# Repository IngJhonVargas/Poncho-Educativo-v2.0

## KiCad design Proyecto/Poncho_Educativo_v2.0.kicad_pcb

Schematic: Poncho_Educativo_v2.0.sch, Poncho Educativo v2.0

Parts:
F1, F2, F3: FIDUCIAL; Fiducial_1mm

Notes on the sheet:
Fiduciales

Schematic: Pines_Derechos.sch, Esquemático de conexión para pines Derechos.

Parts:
AFF1: CA56-12; Cx56-12; Digikey# 67-1442-ND
M1: Matrix_8x8_LED; Matrix_8x8_LEDs; Digikey# TA15-11EWA-ND
R1, R2: 9.53k; R_0805_HandSoldering; Digikey# P21131TR-ND
U1, U2: MAX7219; Digikey# MAX7219CWG+-ND
XA2: Conn_Poncho2P_2x_20x2; Conn_Poncho_Derecha

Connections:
+5V: R1.1, R2.2, U1.19 (Vcc), U2.19 (Vcc), XA2.2 (+5V); also elsewhere on the board
/Pines Derechos/C0: M1.9, U2.2 (DIG0)
/Pines Derechos/C1: M1.10, U2.11 (DIG1)
/Pines Derechos/C2: M1.14, U2.6 (DIG2)
/Pines Derechos/C3: M1.3, U2.7 (DIG3)
/Pines Derechos/C4: M1.15, U2.3 (DIG4)
/Pines Derechos/C5: M1.5, U2.10 (DIG5)
/Pines Derechos/C6: M1.6, U2.5 (DIG6)
/Pines Derechos/C7: M1.12, U2.8 (DIG7)
/Pines Derechos/CLK: U1.13 (CLK), U2.13 (CLK), XA2.33 (tecF0)
/Pines Derechos/D0: AFF1.12 (CA1), U1.2 (DIG0)
/Pines Derechos/D1: AFF1.9 (CA2), U1.11 (DIG1)
/Pines Derechos/D2: AFF1.8 (CA3), U1.6 (DIG2)
/Pines Derechos/D3: AFF1.6 (CA4), U1.7 (DIG3)
/Pines Derechos/Din: U1.1 (DIN), U2.1 (DIN), XA2.39 (tecCOL0)
/Pines Derechos/F0: M1.7, U2.14 (SEGa)
/Pines Derechos/F1: M1.2, U2.16 (SEGb)
/Pines Derechos/F2: M1.8, U2.20 (SEGc)
/Pines Derechos/F3: M1.13, U2.23 (SEGd)
/Pines Derechos/F4: M1.1, U2.21 (SEGe)
/Pines Derechos/F5: M1.11, U2.15 (SEGf)
/Pines Derechos/F6: M1.16, U2.17 (SEGg)
/Pines Derechos/F7: M1.4, U2.22 (SEGdp)
/Pines Derechos/LOAD1: U1.12 (LOAD(cs)), XA2.37 (tecF2)
/Pines Derechos/LOAD2: U2.12 (LOAD(cs)), XA2.35 (tecF3)
/Pines Derechos/S0: AFF1.11 (a), U1.14 (SEGa)
/Pines Derechos/S1: AFF1.7 (b), U1.16 (SEGb)
/Pines Derechos/S2: AFF1.4 (c), U1.20 (SEGc)
/Pines Derechos/S3: AFF1.2 (d), U1.23 (SEGd)
/Pines Derechos/S4: AFF1.1 (e), U1.21 (SEGe)
/Pines Derechos/S5: AFF1.10 (f), U1.15 (SEGf)
/Pines Derechos/S6: AFF1.5 (g), U1.17 (SEGg)
/Pines Derechos/S7: AFF1.3 (DP), U1.22 (SEGdp)
unnamed 45: R1.2; also elsewhere on the board
unnamed 47: R2.1; also elsewhere on the board
unnamed 52: U1.18 (ISET); also elsewhere on the board
unnamed 53: U2.18 (ISET); also elsewhere on the board

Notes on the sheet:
GND con etiqueta global para el MAX7219 de la matriz de LEDs
En los Integrados MAX7219: Los cátodos son - DIG0 al DIG 7. Los ánodos son SEGa al SEGg y SEGdp

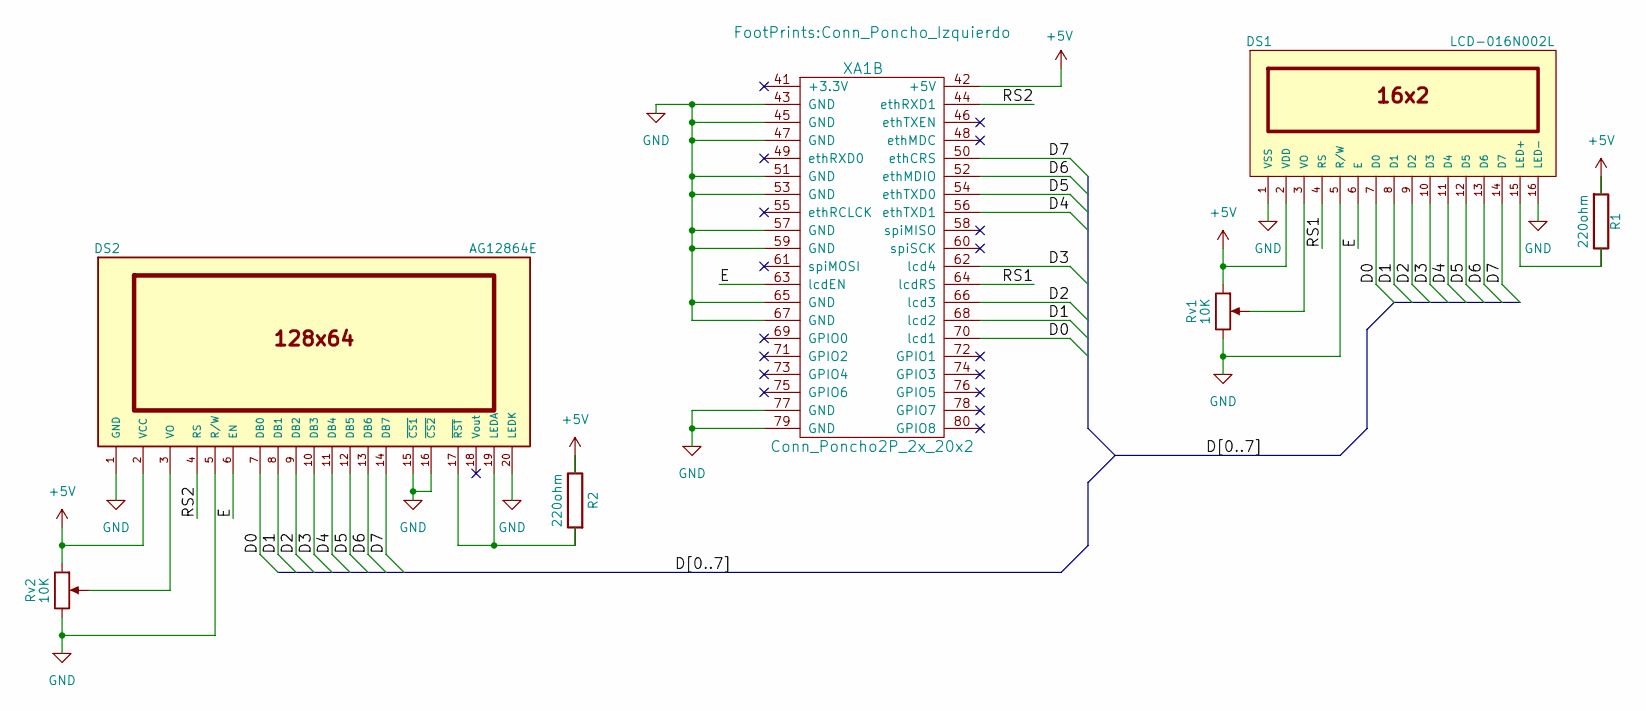
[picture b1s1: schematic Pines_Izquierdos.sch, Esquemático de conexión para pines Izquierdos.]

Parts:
DS1: LCD-016N002L; Digikey# NHD-0216K1Z-NS(RGB)-FBW-REV1-ND
DS2: AG12864E; Digikey# NHD-12864WG-BTMI-V#N-ND
R1, R2: 220ohm; R_0805_HandSoldering; Digikey# P20941TR-ND
Rv1, Rv2: 10K; POT_SMD; Digikey# 3310P-025-103L-ND
XA1: Conn_Poncho2P_2x_20x2; Conn_Poncho_Izquierdo

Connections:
+5V: DS1.2 (VDD), DS2.2 (VCC), R1.1, R2.2, Rv1.1, Rv2.1, XA1.42 (+5V); also elsewhere on the board
/Pines Izquierdos/D0: DS1.7 (D0), DS2.7 (DB0), XA1.70 (lcd1)
/Pines Izquierdos/D1: DS1.8 (D1), DS2.8 (DB1), XA1.68 (lcd2)
/Pines Izquierdos/D2: DS1.9 (D2), DS2.9 (DB2), XA1.66 (lcd3)
/Pines Izquierdos/D3: DS1.10 (D3), DS2.10 (DB3), XA1.62 (lcd4)
/Pines Izquierdos/D4: DS1.11 (D4), DS2.11 (DB4), XA1.56 (ethTXD1)
/Pines Izquierdos/D5: DS1.12 (D5), DS2.12 (DB5), XA1.54 (ethTXD0)
/Pines Izquierdos/D6: DS1.13 (D6), DS2.13 (DB6), XA1.52 (ethMDIO)
/Pines Izquierdos/D7: DS1.14 (D7), DS2.14 (DB7), XA1.50 (ethCRS)
/Pines Izquierdos/E: DS1.6 (E), DS2.6 (EN), XA1.63 (lcdEN)
/Pines Izquierdos/RS1: DS1.4 (RS), XA1.64 (lcdRS)
/Pines Izquierdos/RS2: DS2.4 (RS), XA1.44 (ethRXD1)
unnamed: DS1.3 (VO), Rv1.2
unnamed: DS1.15 (LED+), R1.2
unnamed: DS2.3 (VO), Rv2.2
unnamed: DS2.17 (~RST~), DS2.19 (LEDA), R2.1

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
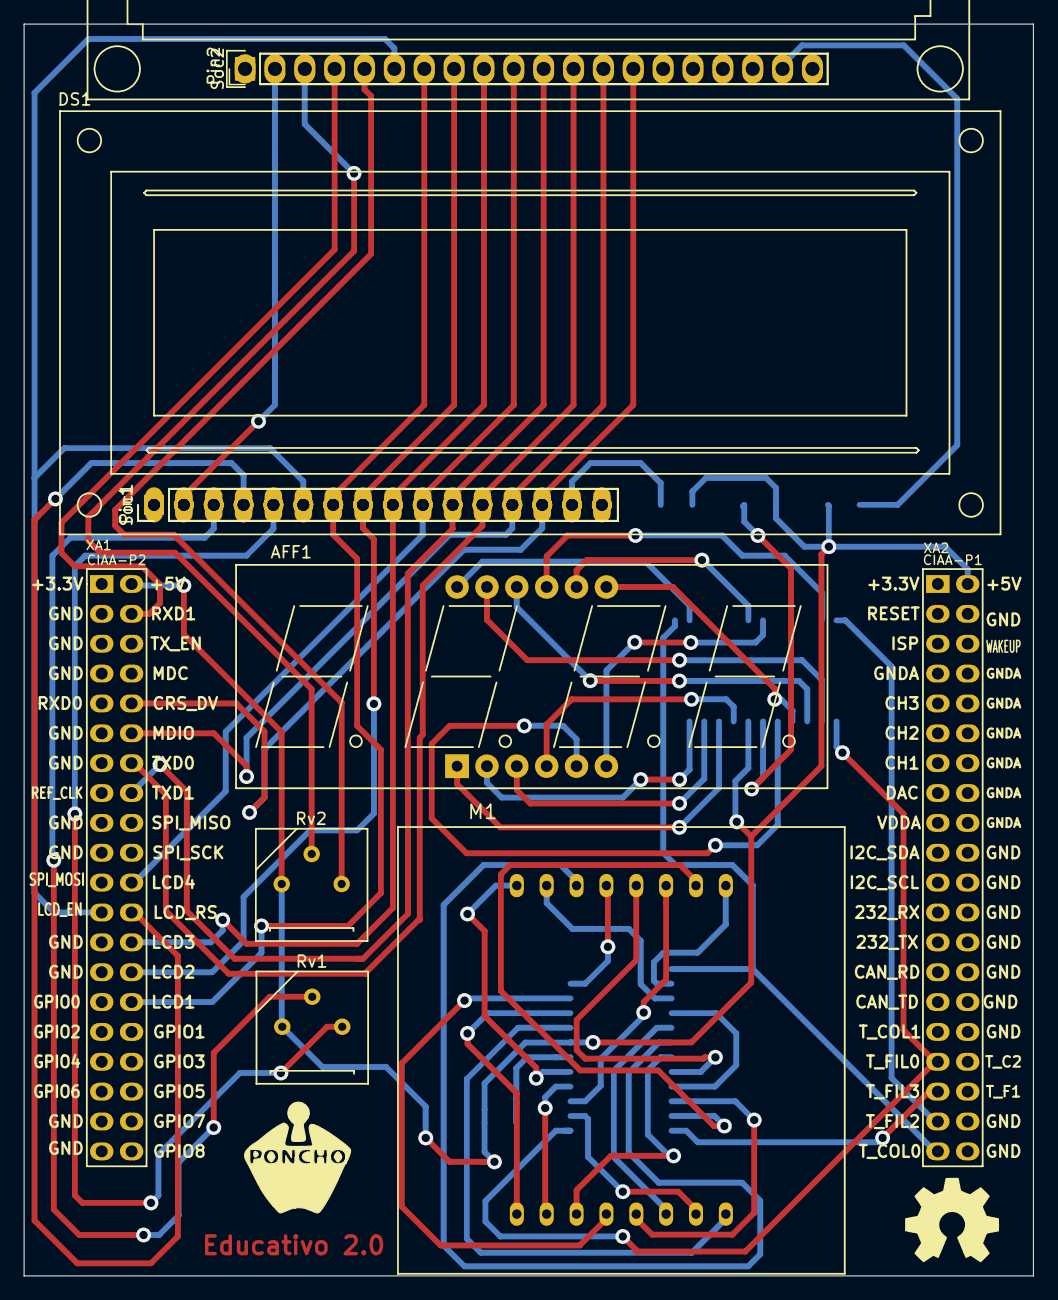
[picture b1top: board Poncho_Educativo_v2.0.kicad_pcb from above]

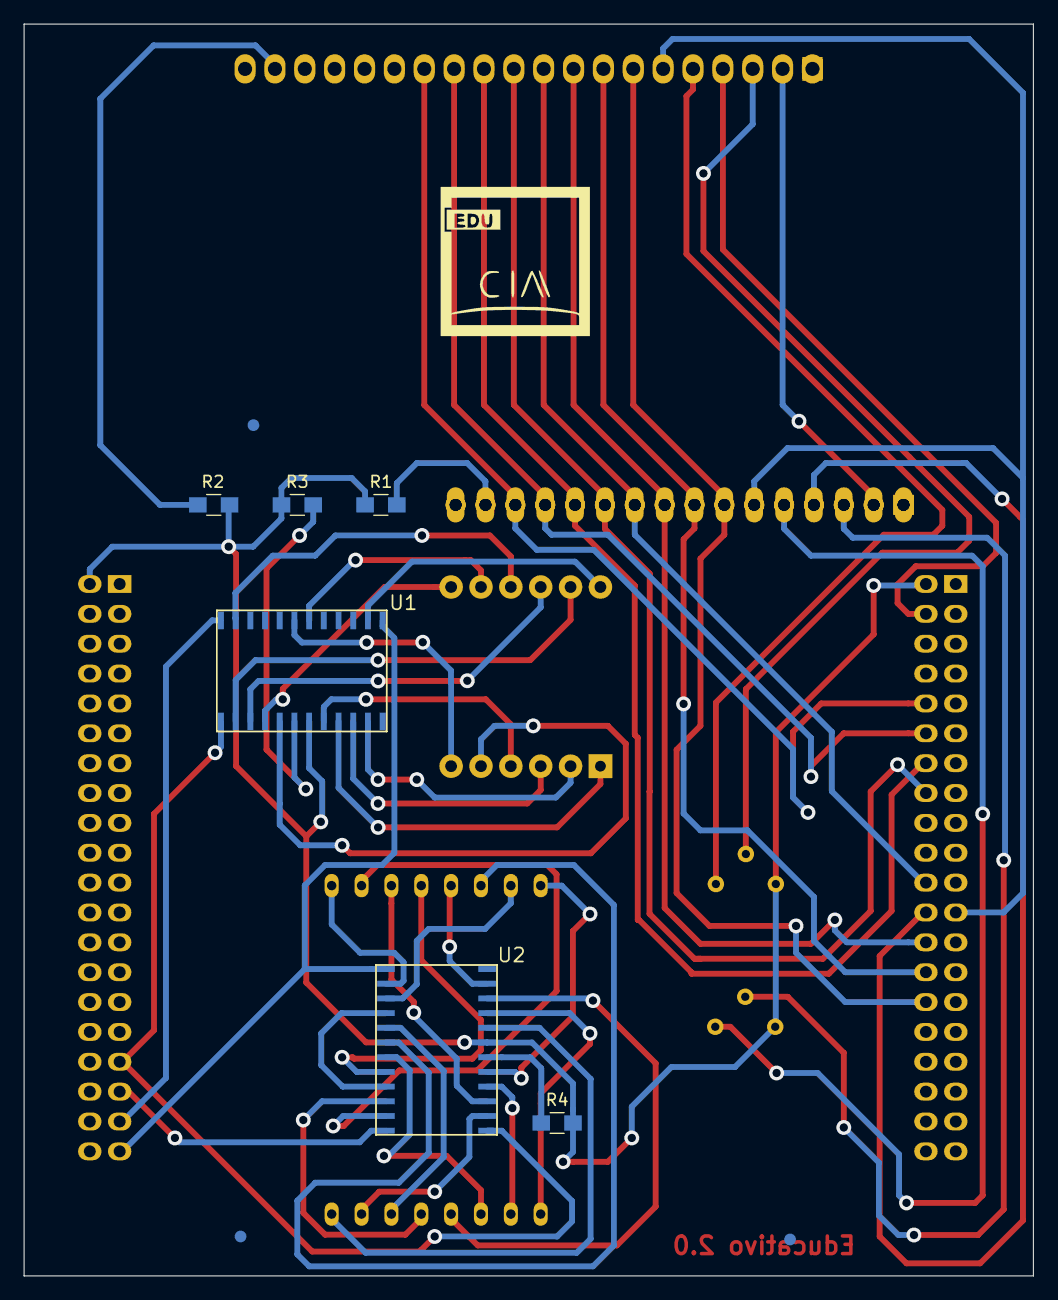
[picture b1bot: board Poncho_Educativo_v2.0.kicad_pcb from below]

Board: 2 copper layers, 85.9 x 106.5 mm, 22 parts (9 on the bottom side), 57 nets.

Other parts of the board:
G101: Logo_OSHWA
Pin1: Pin_Header_Straight_1x16_Pitch2.54mm
Pin2: CONN_01X20; Pin_Header_Straight_1x20
R3, R4: 9.53k; R_0805_HandSoldering
Soc1: Socket_Strip_Straight_1x16_Pitch2.54mm
Soc2: Socket_Strip_Straight_1x20_Pitch2.54mm

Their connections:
+5V: R3.1, R4.1; also elsewhere on the board
unnamed 52: R3.2; also elsewhere on the board
unnamed 53: R4.2; also elsewhere on the board

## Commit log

2017-05-09 Componentes principales.
    Se especificaron los principales componentes que llevará el Poncho
    Educativo v2.0.
2017-05-09 Displays LCD
    Se adjuntó documentación acerca de los 2 Displays LCD.
2017-05-16 Carpetas de displays.
    Se añadieron 2 carpetas para guardar la documentación referente al
    diaplay BCD de 4 digitos y a la matriz de leds 8x8.
2017-05-16 Carpeta principal del Proyecto
    Se organizaron las principales carpetas de las librerías para el Poncho
    Mediano y se crearon los primeros archivos del esquemático principal.
    (Modificación del Rotulo).
2017-05-23 Diseño de esquematico - Pines Izquierdos
    Se inició el diseño del esquematico de los pines Izquierdos de la
    EDU-CIAA y se agregaron librerias y FootPrints.
2017-05-26 Actualización de documentación y esquemáticos.
    Se actualizaron los archivos de datos y caracteristicas de los displays
    y se adelantó a un 90% el diseño de los esquemáticos de KiCad.
2017-05-28 Avance de FootPrints
    Se terminó diseño de esquemáticos en ojas Jerárquicas; se avanzó a un
    70% en las referencias de FootPrint, y se actualizaron hojas de datos de
    la Matriz de LEDs 8x8.
2017-06-12 Modelos 3D
    Se modificaron FootPrints y se agregaron modelos en 3D.
2017-07-15 Ruteo y 3D
    Se realizó el ruteo completo y se agregaron modelos 3D
2017-08-09 Modificación de path de shapes3D
    Se modificó el path de shapes3D.
2017-08-09 Modificación de path de shapes3D
